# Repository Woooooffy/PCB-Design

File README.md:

# PCB-Design
# Contains my project files
# Hug-sensing IoT plush: a pair of plushies that detects hugs on one end and triggers response in the other. Inspired by Becky and Xyla's project https://beckystern.com/2023/11/27/hug-sensing-iot-parihug-toy-w-xyla-foxlin/ and part of the MIT 2024 PCB design class

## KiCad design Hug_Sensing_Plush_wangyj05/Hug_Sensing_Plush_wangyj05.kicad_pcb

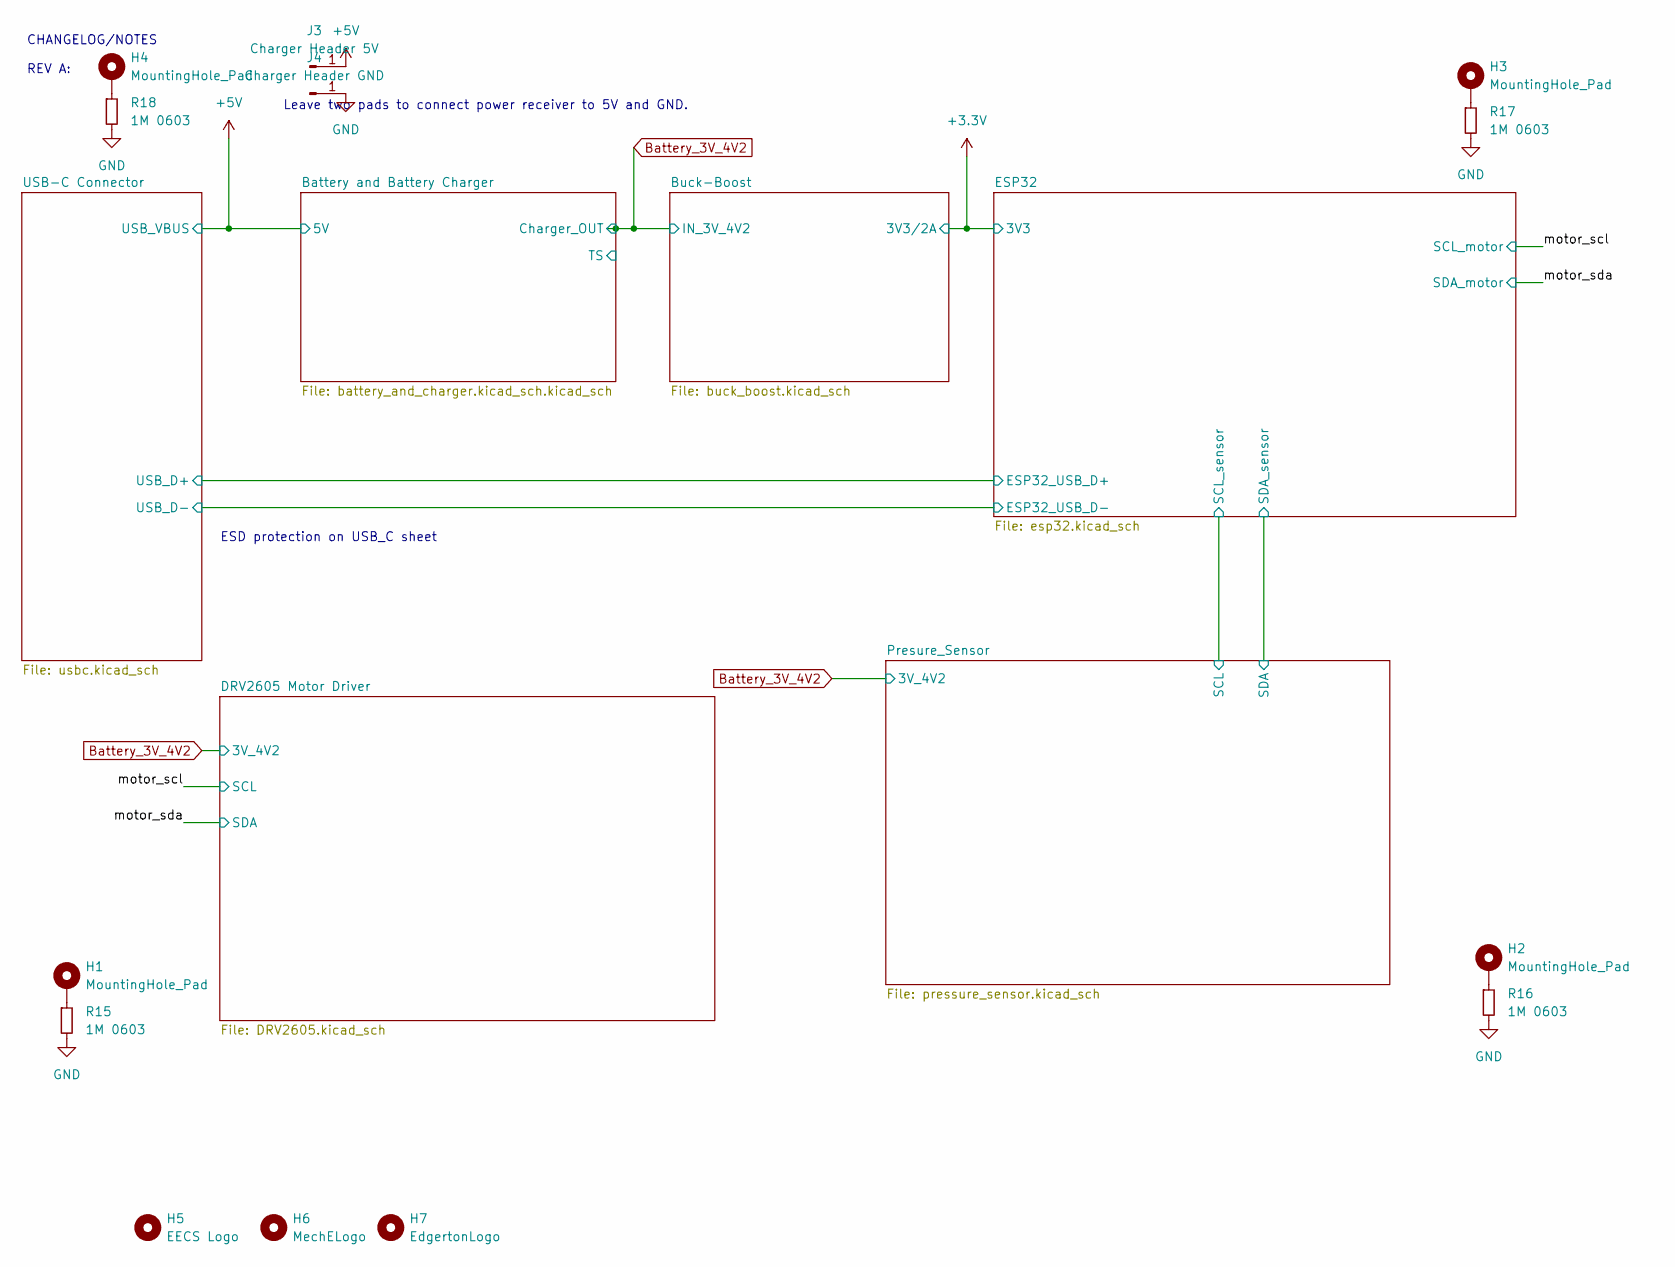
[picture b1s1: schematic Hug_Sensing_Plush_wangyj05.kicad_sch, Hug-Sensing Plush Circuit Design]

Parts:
H1, H2, H3, H4: MountingHole_Pad; MountingHole_2.2mm_M2_DIN965_Pad
H5: EECS Logo; EECSLogo
H6: MechELogo
H7: EdgertonLogo
J3: Charger Header 5V; SolderWirePad_1x01_SMD_1x2mm
J4: Charger Header GND; SolderWirePad_1x01_SMD_1x2mm
R15, R16, R17, R18: 1M 0603; R_0603_1608Metric_Pad0.98x0.95mm_HandSolder; MPN CRCW06031M00JNEAC; Digikey PN 541-CRCW06031M00JNEACCT-ND

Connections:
+5V: J3.1; also elsewhere on the board
GND: J4.1, R15.2, R16.2, R17.2, R18.2; also elsewhere on the board
unnamed: H1.1, R15.1
unnamed: H2.1, R16.1
unnamed: H3.1, R17.1
unnamed: H4.1, R18.1

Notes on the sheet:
ESD protection on USB_C sheet
Leave two pads to connect power receiver to 5V and GND.
CHANGELOG/NOTES REV A:

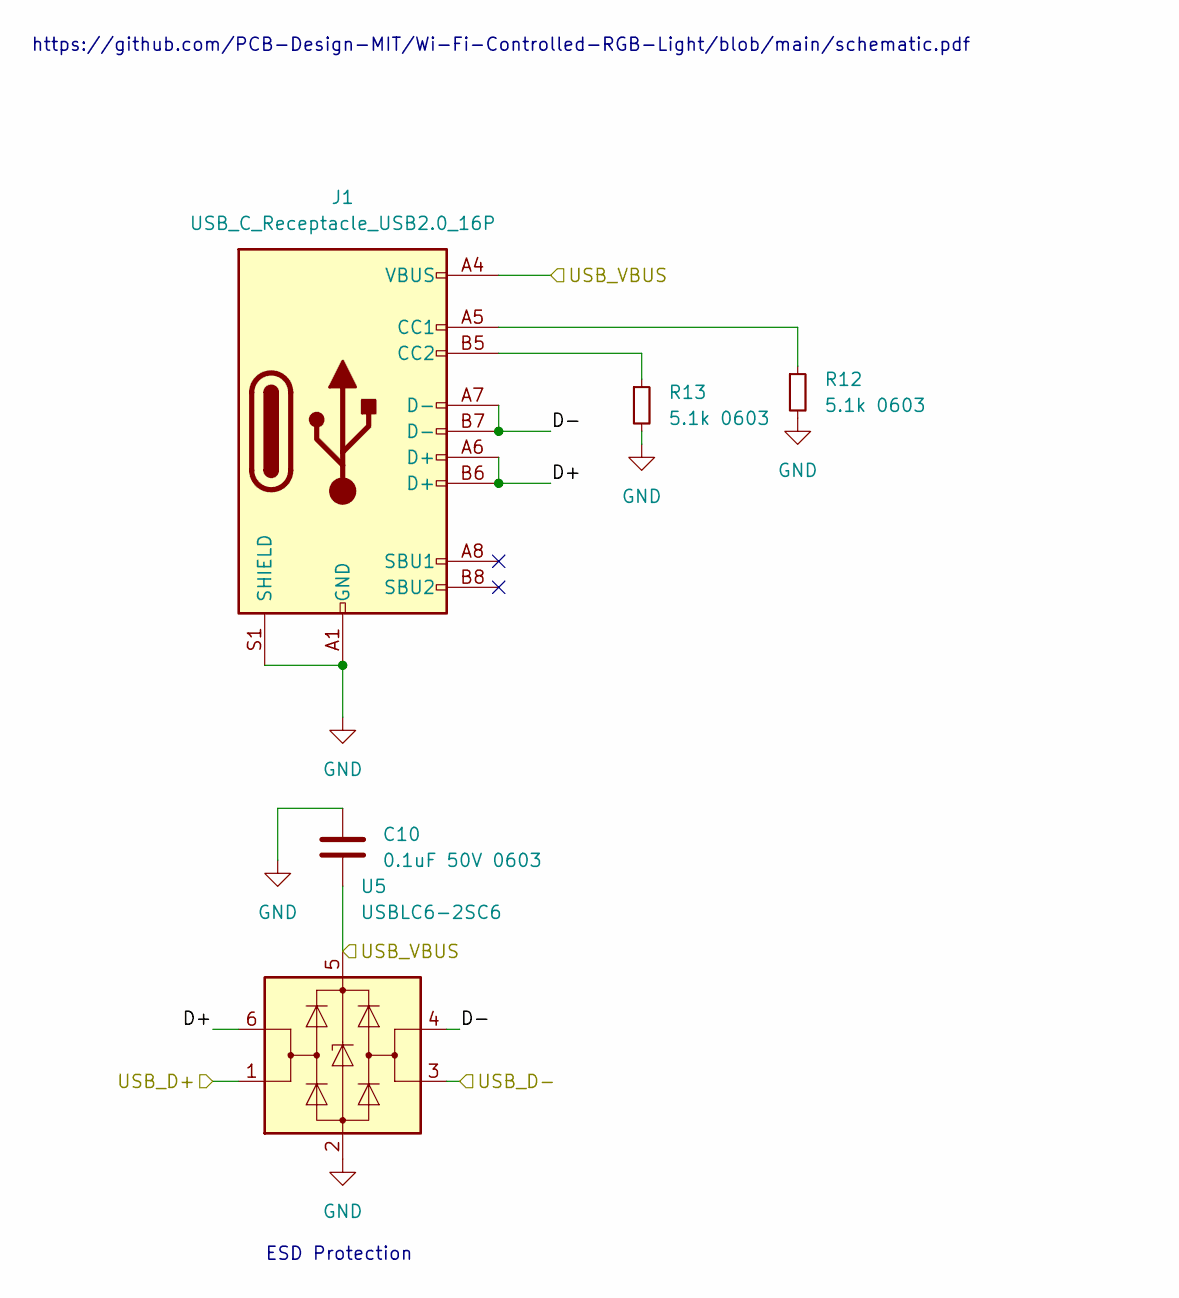
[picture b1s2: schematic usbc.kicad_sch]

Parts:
C10: 0.1uF 50V 0603; C_0603_1608Metric_Pad1.08x0.95mm_HandSolder; MPN CL10B104KB8NNNL; Digikey PN 1276-CL10B104KB8NNNLCT-ND
J1: USB_C_Receptacle_USB2.0_16P; USB_C_Receptacle_GCT_USB4085; MPN USB4085-GF-A; Digikey PN 2073-USB4085-GF-ACT-ND
R12, R13: 5.1k 0603; R_0603_1608Metric_Pad0.98x0.95mm_HandSolder; MPN CRCW06035K10FKEBC; Digikey PN 541-CRCW06035K10FKEBCDKR-ND
U5: USBLC6-2SC6; SOT-23-6; MPN USBLC6-2SC6; Digikey PN 497-5235-1-ND

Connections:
+5V: C10.2, J1.A4 (VBUS), J1.A9 (VBUS), J1.B4 (VBUS), J1.B9 (VBUS), U5.5 (VBUS); also elsewhere on the board
/ESP32/ESP32_USB_D+: U5.1 (I/O1); also elsewhere on the board
/ESP32/ESP32_USB_D-: U5.3 (I/O2); also elsewhere on the board
/USB-C Connector/D+: J1.A6 (D+), J1.B6 (D+), U5.6 (I/O1)
/USB-C Connector/D-: J1.A7 (D-), J1.B7 (D-), U5.4 (I/O2)
GND: C10.1, J1.A1 (GND), J1.A12 (GND), J1.B1 (GND), J1.B12 (GND), J1.S1 (SHIELD), R12.2, R13.2, U5.2 (GND); also elsewhere on the board
unnamed: J1.A5 (CC1), R12.1
unnamed: J1.B5 (CC2), R13.1

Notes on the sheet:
https://github.com/PCB-Design-MIT/Wi-Fi-Controlled-RGB-Light/blob/main/schematic.pdf
ESD Protection

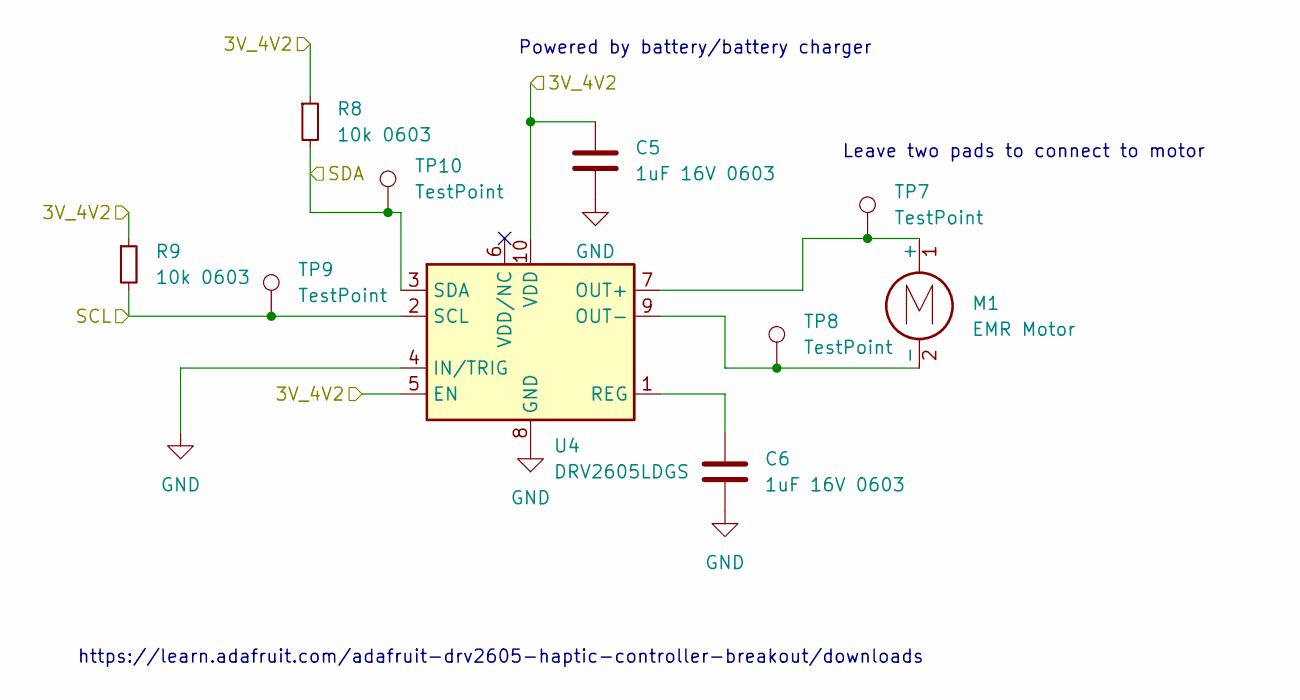
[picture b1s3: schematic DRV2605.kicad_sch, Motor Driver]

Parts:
C5, C6: 1uF 16V 0603; C_0603_1608Metric_Pad1.08x0.95mm_HandSolder; MPN CL10A105KO8NNNC; Digikey PN 1276-1034-1-ND
M1: EMR Motor; MPN 1201; Digikey PN 1528-1177-ND
R8, R9: 10k 0603; R_0603_1608Metric_Pad0.98x0.95mm_HandSolder; MPN CRCW060310K0FKEA; Digikey PN 541-10.0KHCT-ND
TP7, TP8, TP9, TP10: TestPoint; TestPoint_Keystone_5015_Micro-Minature; MPN RCWCTE; Digikey PN 2019-RCWCTECT-ND
U4: DRV2605LDGS; VSSOP-10_3x3mm_P0.5mm; MPN DRV2605LDGSR; Digikey PN 296-40032-1-ND

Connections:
/motor_scl: R9.2, TP9.1, U4.2 (SCL); also elsewhere on the board
/motor_sda: R8.2, TP10.1, U4.3 (SDA); also elsewhere on the board
Battery_3V_4V2: C5.1, R8.1, R9.1, U4.5 (EN), U4.10 (VDD); also elsewhere on the board
GND: C5.2, C6.2, U4.4 (IN/TRIG), U4.8 (GND); also elsewhere on the board
unnamed: M1.1 (+), TP7.1, U4.7 (OUT+)
unnamed: M1.2 (-), TP8.1, U4.9 (OUT-)
unnamed: C6.1, U4.1 (REG)

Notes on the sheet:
https://learn.adafruit.com/adafruit-drv2605-haptic-controller-breakout/downloads
Leave two pads to connect to motor
Powered by battery/battery charger

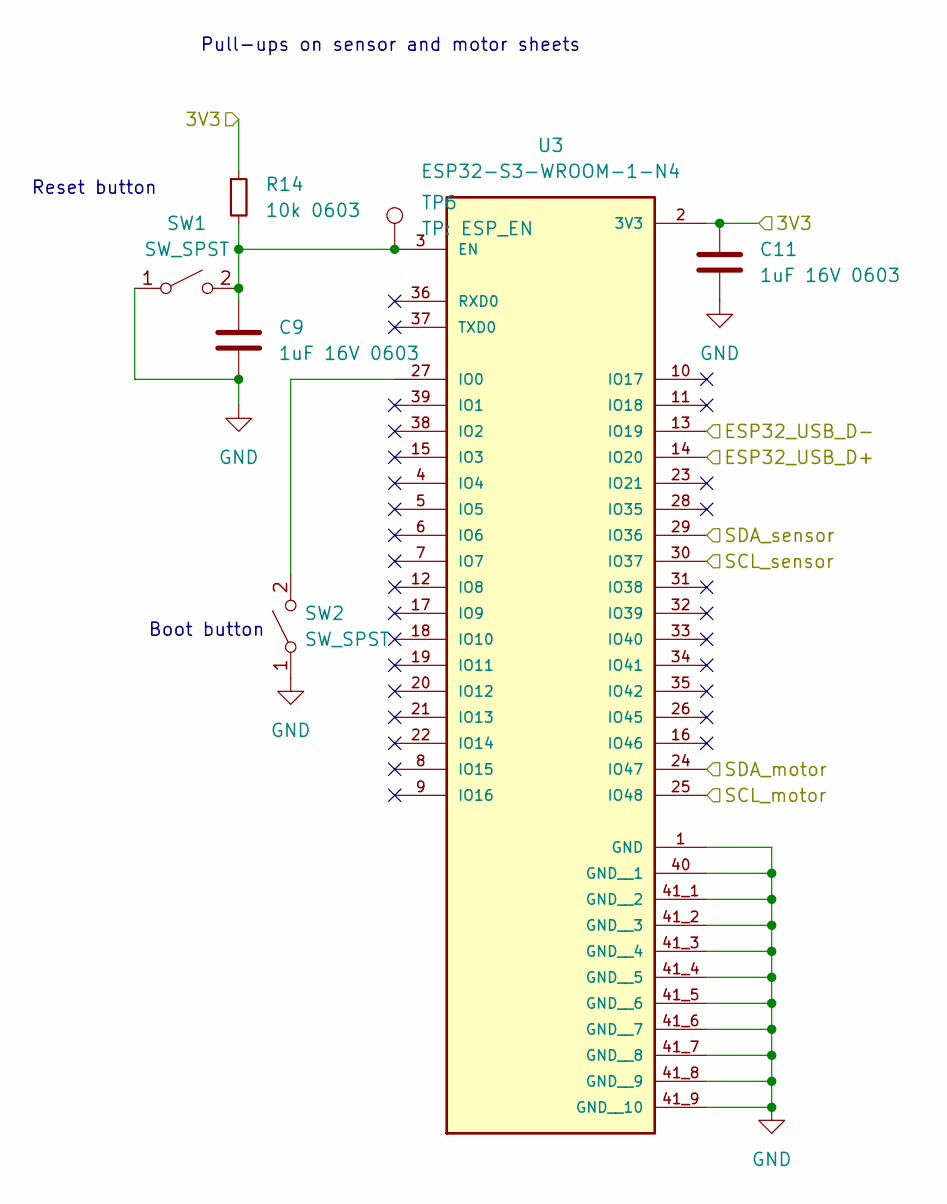
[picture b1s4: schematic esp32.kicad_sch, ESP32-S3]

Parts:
C9, C11: 1uF 16V 0603; C_0603_1608Metric_Pad1.08x0.95mm_HandSolder; MPN CL10A105KO8NNNC; Digikey PN 1276-1034-1-ND
R14: 10k 0603; R_0603_1608Metric_Pad0.98x0.95mm_HandSolder; MPN CRCW060310K0FKEA; Digikey PN 541-10.0KHCT-ND
SW1, SW2: SW_SPST; SW_SPST_FSMSM
TP6: TP: ESP_EN; TestPoint_Keystone_5015_Micro-Minature; MPN RCWCTE; Digikey PN 2019-RCWCTECT-ND
U3: ESP32-S3-WROOM-1-N4; ESP32-S3; PARTREV v1.0; Digikey PN 1965-ESP32-S3-WROOM-1-N4CT-ND

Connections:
+3.3V: C11.1, R14.1, U3.2 (3V3); also elsewhere on the board
/ESP32/ESP32_USB_D+: U3.14 (IO20); also elsewhere on the board
/ESP32/ESP32_USB_D-: U3.13 (IO19); also elsewhere on the board
/ESP32/SCL_sensor: U3.30 (IO37); also elsewhere on the board
/ESP32/SDA_sensor: U3.29 (IO36); also elsewhere on the board
/motor_scl: U3.25 (IO48); also elsewhere on the board
/motor_sda: U3.24 (IO47); also elsewhere on the board
GND: C9.2, C11.2, SW1.1 (A), SW2.1 (A), U3.1 (GND), U3.40 (GND__1), U3.41_1 (GND__2), U3.41_2 (GND__3), U3.41_3 (GND__4), U3.41_4 (GND__5), U3.41_5 (GND__6), U3.41_6 (GND__7), U3.41_7 (GND__8), U3.41_8 (GND__9), U3.41_9 (GND__10), U3.41_10, U3.41_11, U3.41_12, U3.41_13, U3.41_14, U3.41_15, U3.41_16, U3.41_17, U3.41_18, U3.41_19, U3.41_20, U3.41_21; also elsewhere on the board
unnamed: C9.1, R14.2, SW1.2 (B), TP6.1, U3.3 (EN)
unnamed: SW2.2 (B), U3.27 (IO0)

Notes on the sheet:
Pull-ups on sensor and motor sheets
Boot button
Reset button

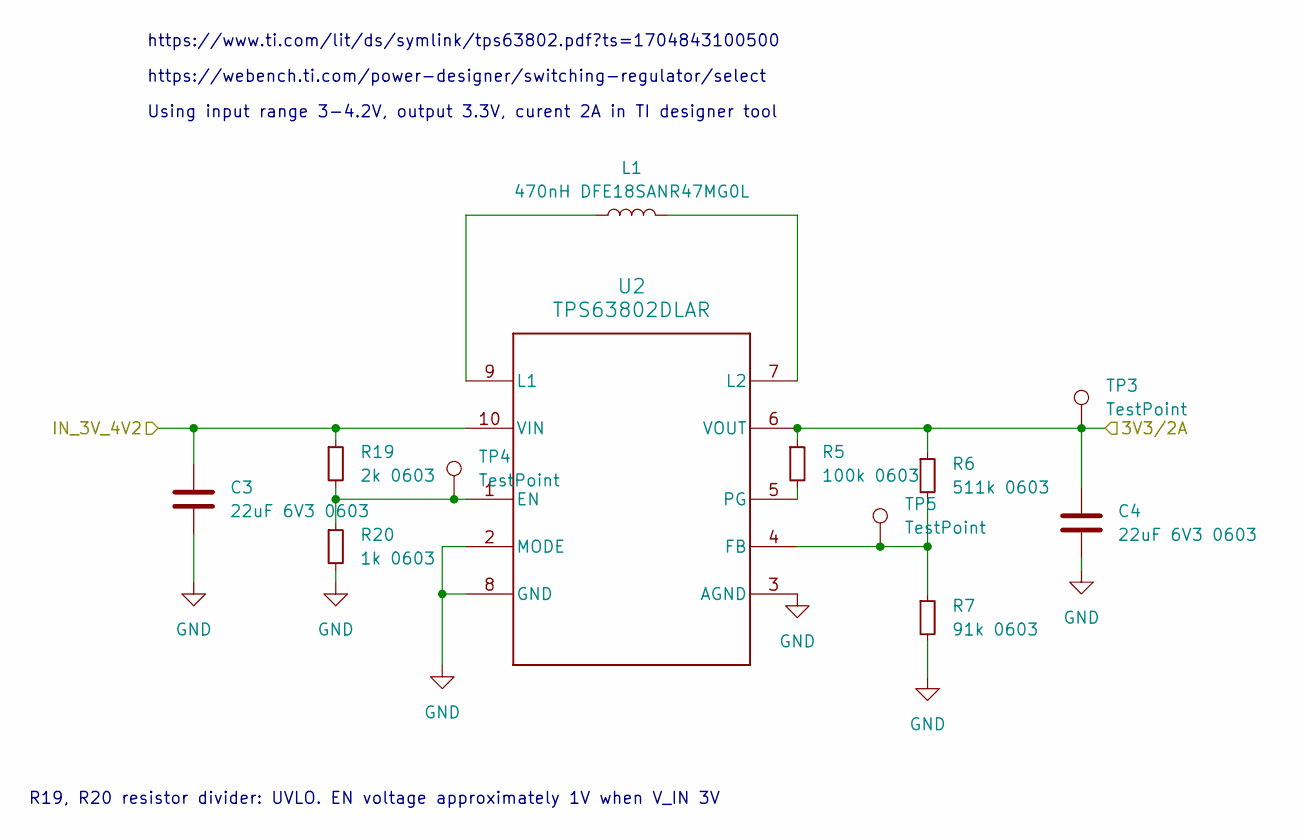
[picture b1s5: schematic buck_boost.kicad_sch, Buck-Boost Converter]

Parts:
C3, C4: 22uF 6V3 0603; C_0603_1608Metric_Pad1.08x0.95mm_HandSolder; MPN GRM188R60J226MEA0; Digikey PN 490-7612-2-ND
L1: 470nH DFE18SANR47MG0L; L_0603_1608Metric_Pad1.05x0.95mm_HandSolder; MPN DFE18SANR47MG0L; Digikey PN 490-16581-1-ND
R5: 100k 0603; R_0603_1608Metric_Pad0.98x0.95mm_HandSolder; MPN CRCW0603100KFKEA; Digikey PN 541-100KHCT-ND
R6: 511k 0603; R_0603_1608Metric_Pad0.98x0.95mm_HandSolder; MPN CRCW0603511KFKEA; Digikey PN 541-511KHCT-ND
R7: 91k 0603; R_0603_1608Metric_Pad0.98x0.95mm_HandSolder; MPN CRCW060391K0FKEAC; Digikey PN 541-5595-1-ND
R19: 2k 0603; R_0603_1608Metric_Pad0.98x0.95mm_HandSolder; MPN CRCW06032K00FKEB; Digikey PN 541-CRCW06032K00FKEBCT-ND
R20: 1k 0603; R_0603_1608Metric_Pad0.98x0.95mm_HandSolder; MPN CRCW06031K00FKEA; Digikey PN 541-1.00KHCT-ND
TP3, TP4, TP5: TestPoint; TestPoint_Keystone_5015_Micro-Minature; MPN RCWCTE; Digikey PN 2019-RCWCTECT-ND
U2: TPS63802DLAR; TPS63802; MPN TPS63802DLAR; Digikey PN 296-TPS63802DLARCT-ND

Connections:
+3.3V: C4.1, R5.1, R6.1, TP3.1, U2.6 (VOUT); also elsewhere on the board
Battery_3V_4V2: C3.1, R19.1, U2.10 (VIN); also elsewhere on the board
GND: C3.2, C4.2, R7.2, R20.2, U2.2 (MODE), U2.3 (AGND), U2.8 (GND); also elsewhere on the board
unnamed: R19.2, R20.1, TP4.1, U2.1 (EN)
unnamed: R6.2, R7.1, TP5.1, U2.4 (FB)
unnamed: L1.1, U2.9 (L1)
unnamed: L1.2, U2.7 (L2)
unnamed: R5.2, U2.5 (PG)

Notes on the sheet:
https://webench.ti.com/power-designer/switching-regulator/select
https://www.ti.com/lit/ds/symlink/tps63802.pdf?ts=1704843100500
R19, R20 resistor divider: UVLO. EN voltage approximately 1V when V_IN 3V
Using input range 3-4.2V, output 3.3V, curent 2A in TI designer tool

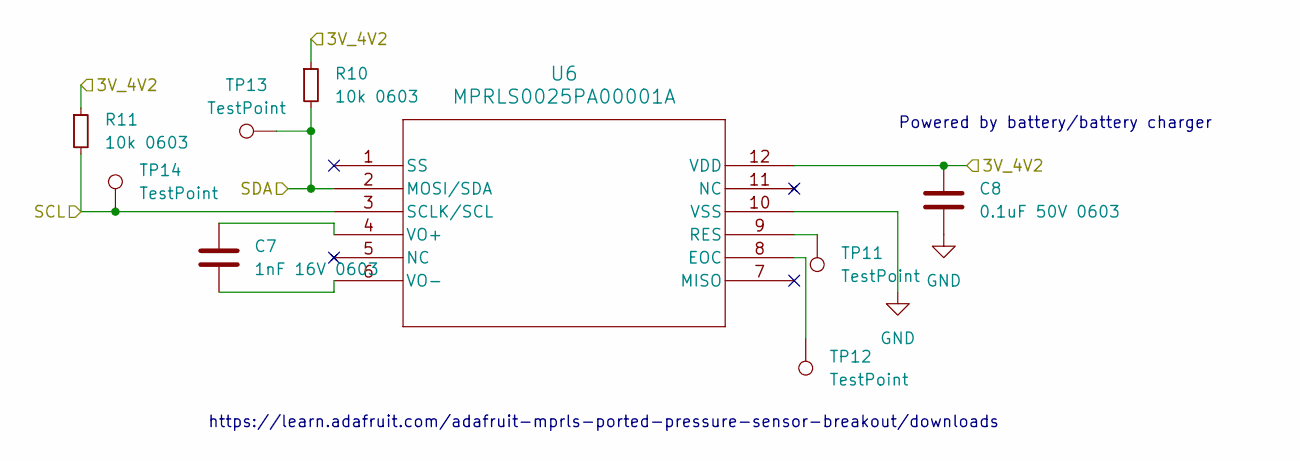
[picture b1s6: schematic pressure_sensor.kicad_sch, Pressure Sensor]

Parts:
C7: 1nF 16V 0603; C_0603_1608Metric_Pad1.08x0.95mm_HandSolder; MPN C0603C102K4RECAUTO; Digikey PN 399-17878-1-ND
C8: 0.1uF 50V 0603; C_0603_1608Metric_Pad1.08x0.95mm_HandSolder; MPN CL10B104KB8NNNL; Digikey PN 1276-CL10B104KB8NNNLCT-ND
R10, R11: 10k 0603; R_0603_1608Metric_Pad0.98x0.95mm_HandSolder; MPN CRCW060310K0FKEA; Digikey PN 541-10.0KHCT-ND
TP11, TP12, TP13, TP14: TestPoint; TestPoint_Keystone_5015_Micro-Minature; MPN RCWCTE; Digikey PN 2019-RCWCTECT-ND
U6: MPRLS0025PA00001A; MPRLS; MPN MPRLS0025PA00001A; Digikey PN 480-7098-1-ND

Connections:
/ESP32/SCL_sensor: R11.2, TP14.1, U6.3 (SCLK/SCL); also elsewhere on the board
/ESP32/SDA_sensor: R10.2, TP13.1, U6.2 (MOSI/SDA); also elsewhere on the board
Battery_3V_4V2: C8.1, R10.1, R11.1, U6.12 (VDD); also elsewhere on the board
GND: C8.2, U6.10 (VSS); also elsewhere on the board
unnamed: TP12.1, U6.8 (EOC)
unnamed: TP11.1, U6.9 (RES)
unnamed: C7.1, U6.4 (VO+)
unnamed: C7.2, U6.6 (VO-)

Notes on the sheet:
https://learn.adafruit.com/adafruit-mprls-ported-pressure-sensor-breakout/downloads
Powered by battery/battery charger

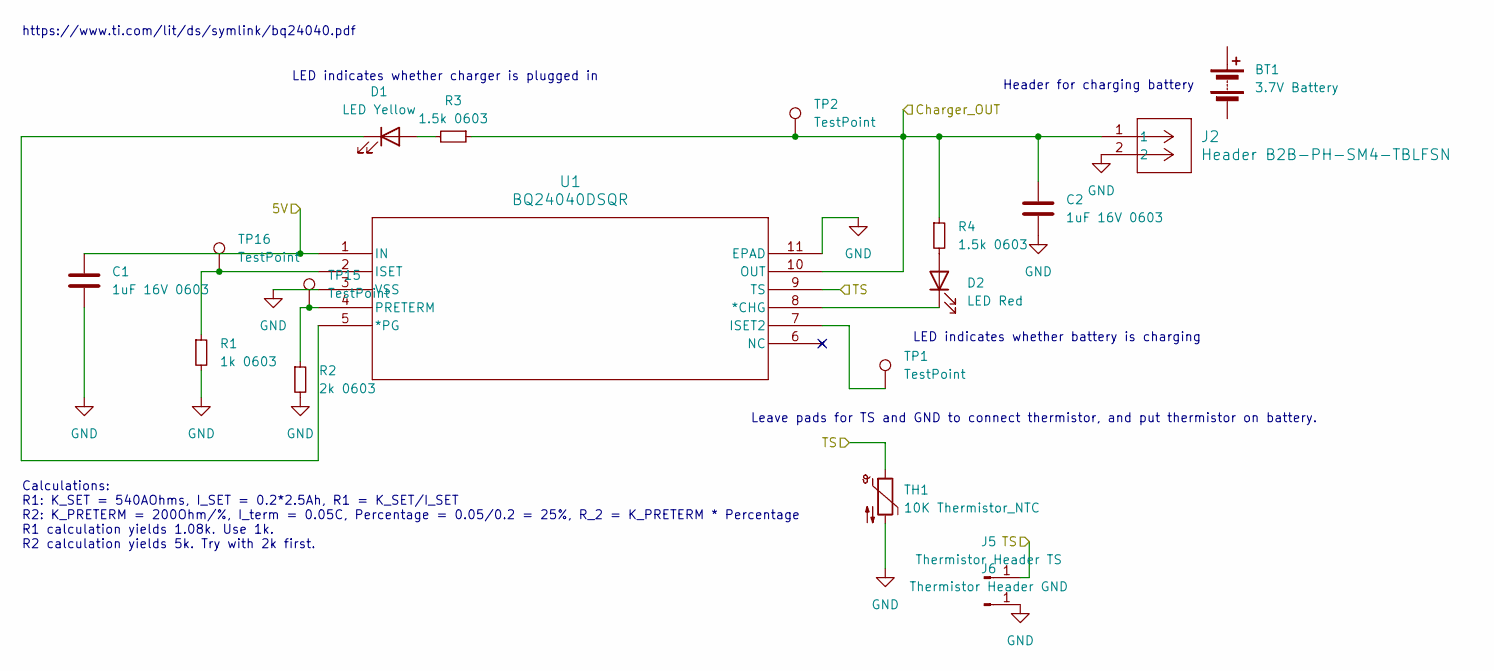
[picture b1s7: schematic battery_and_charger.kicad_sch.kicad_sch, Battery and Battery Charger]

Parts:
BT1: 3.7V Battery; MPN 328; Digikey PN 1528-1840-ND
C1, C2: 1uF 16V 0603; C_0603_1608Metric_Pad1.08x0.95mm_HandSolder; MPN CL10A105KO8NNNC; Digikey PN 1276-1034-1-ND
D1: LED Yellow; LED_0603_1608Metric_Pad1.05x0.95mm_HandSolder; MPN LTST-C190KSKT; Digikey PN 160-1437-1-ND
D2: LED Red; LED_0603_1608Metric_Pad1.05x0.95mm_HandSolder; MPN LTST-C190EKT; Digikey PN 160-1182-1-ND
J2: Header B2B-PH-SM4-TBLFSN; CONN_B2B-PH-SM4-TBLFSN_JST(Header); MPN B2B-PH-SM4-TB; Digikey PN 455-B2B-PH-SM4-TBCT-ND
J5: Thermistor Header TS; SolderWirePad_1x01_SMD_1x2mm
J6: Thermistor Header GND; SolderWirePad_1x01_SMD_1x2mm
R1: 1k 0603; R_0603_1608Metric_Pad0.98x0.95mm_HandSolder; MPN CRCW06031K00FKEA; Digikey PN 541-1.00KHCT-ND
R2: 2k 0603; R_0603_1608Metric_Pad0.98x0.95mm_HandSolder; MPN CRCW06032K00FKEB; Digikey PN 541-CRCW06032K00FKEBCT-ND
R3, R4: 1.5k 0603; R_0603_1608Metric_Pad0.98x0.95mm_HandSolder; MPN CRCW06031K50FKEB; Digikey PN 541-CRCW06031K50FKEBCT-ND
TH1: 10K Thermistor_NTC; MPN 4890; Digikey PN 1528-4890-ND
TP1, TP2, TP15, TP16: TestPoint; TestPoint_Keystone_5015_Micro-Minature; MPN RCWCTE; Digikey PN 2019-RCWCTECT-ND
U1: BQ24040DSQR; BQ24040; MPN BQ24040DSQR; Digikey PN 296-37142-1-ND

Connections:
+5V: C1.1, U1.1 (IN); also elsewhere on the board
/Battery and Battery Charger/TS: J5.1, TH1.1, U1.9 (TS)
Battery_3V_4V2: C2.1, J2.1, R3.1, R4.1, TP2.1, U1.10 (OUT); also elsewhere on the board
GND: C1.2, C2.2, J2.2, J2.3, J2.4, J6.1, R1.2, R2.2, TH1.2, U1.3 (VSS), U1.11 (EPAD), U1.V; also elsewhere on the board
unnamed: D1.2 (A), R3.2
unnamed: D1.1 (K), U1.5 (*PG)
unnamed: D2.2 (A), R4.2
unnamed: D2.1 (K), U1.8 (*CHG)
unnamed: TP1.1, U1.7 (ISET2)
unnamed: R1.1, TP16.1, U1.2 (ISET)
unnamed: R2.1, TP15.1, U1.4 (PRETERM)

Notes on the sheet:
Header for charging battery
LED indicates whether battery is charging
Leave pads for TS and GND to connect thermistor, and put thermistor on battery.
Calculations: R1: K_SET = 540AOhms, I_SET = 0.2*2.5Ah, R1 = K_SET/I_SET R2: K_PRETERM = 200Ohm/%, I_term = 0.05C, Percentage = 0.05/0.2 = 25%, R_2 = K_PRETERM * Percentage R1 calculation yields 1.08k. Use 1k. R2 calculation yields 5k. Try with 2k first.
https://www.ti.com/lit/ds/symlink/bq24040.pdf
LED indicates whether charger is plugged in

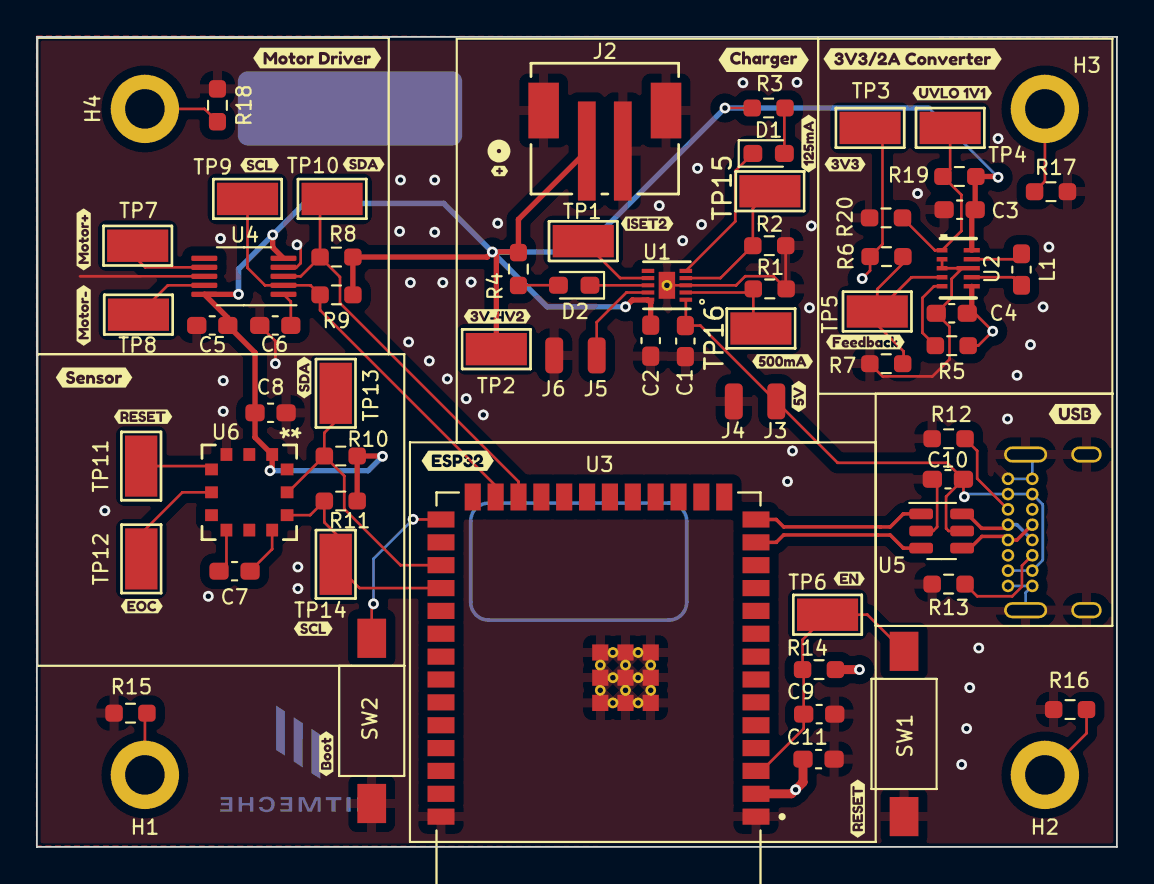
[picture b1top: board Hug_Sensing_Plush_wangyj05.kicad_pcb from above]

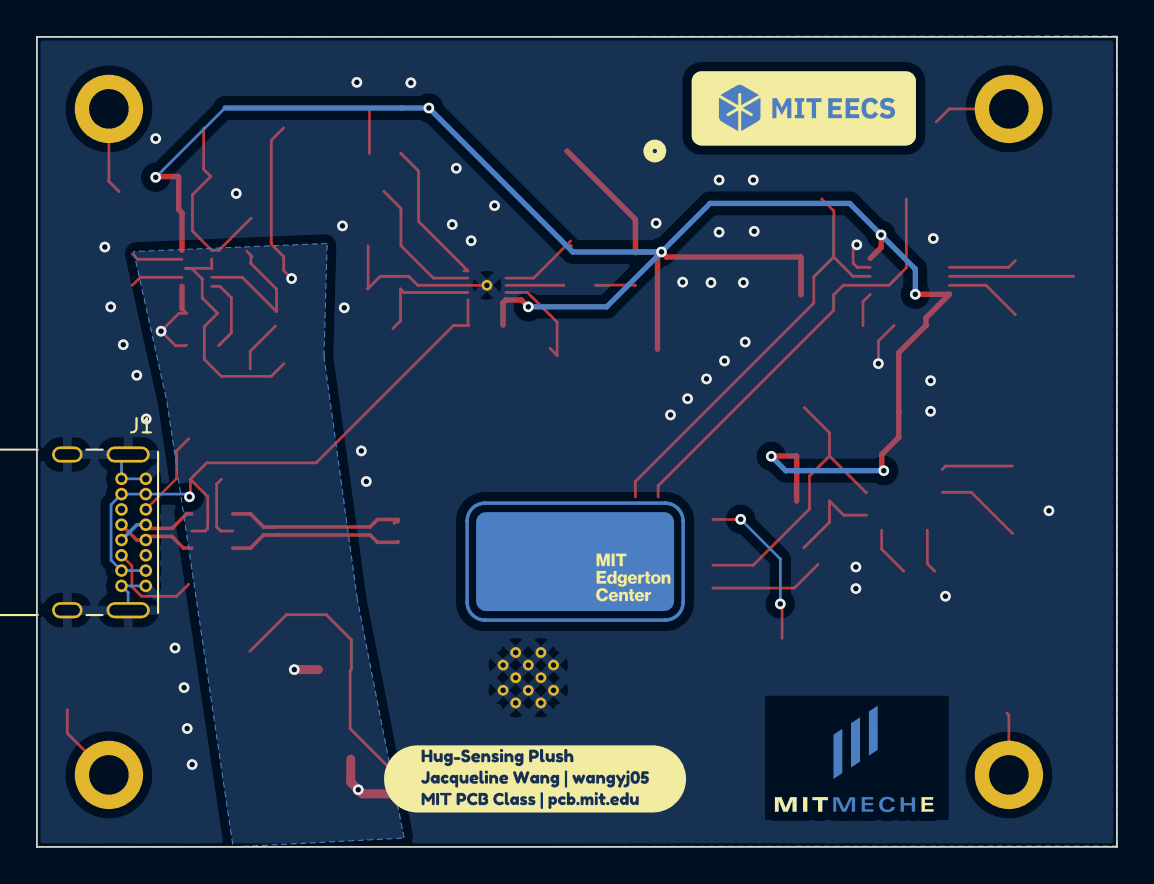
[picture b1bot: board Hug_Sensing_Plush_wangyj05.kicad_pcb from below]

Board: 2 copper layers, 60.0 x 45.0 mm, 98 parts (5 on the bottom side), 40 nets.

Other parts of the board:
kibuzzard-65AAE9C3: G***; kibuzzard-65AAE9C3
kibuzzard-65AAE9E5: G***; kibuzzard-65AAE9E5
kibuzzard-65AAEA4C: G***; kibuzzard-65AAEA4C
kibuzzard-65AAEA37: G***; kibuzzard-65AAEA37
kibuzzard-65AAEA43: G***; kibuzzard-65AAEA43
kibuzzard-65AAEA55: G***; kibuzzard-65AAEA55
kibuzzard-65AAEA96: G***; kibuzzard-65AAEA96
kibuzzard-65AAEAAB: G***; kibuzzard-65AAEAAB
kibuzzard-65AAEAD5: G***; kibuzzard-65AAEAD5
kibuzzard-65AAEADF: G***; kibuzzard-65AAEADF
kibuzzard-65AAEB64: G***; kibuzzard-65AAEB64
kibuzzard-65AAEBD9: G***; kibuzzard-65AAEBD9
kibuzzard-65AAEBEE: G***; kibuzzard-65AAEBEE
kibuzzard-65AAECF1: G***; kibuzzard-65AAECF1
kibuzzard-65AAF1CD: G***; kibuzzard-65AAF1CD
kibuzzard-65AAF1FE: G***; kibuzzard-65AAF1FE
kibuzzard-65AAF2C1: G***; kibuzzard-65AAF2C1
kibuzzard-65AAF2E5: G***; kibuzzard-65AAF2E5
kibuzzard-65AAF3AD: G***; kibuzzard-65AAF3AD
kibuzzard-65AAF7C7: G***; kibuzzard-65AAF7C7
kibuzzard-65AAF38A: G***; kibuzzard-65AAF38A
kibuzzard-65AAF39C: G***; kibuzzard-65AAF39C
kibuzzard-65AAF250: G***; kibuzzard-65AAF250
kibuzzard-65AAF270: G***; kibuzzard-65AAF270
kibuzzard-65AAF304: G***; kibuzzard-65AAF304
kibuzzard-65AAF374: G***; kibuzzard-65AAF374
kibuzzard-65AAF394: G***; kibuzzard-65AAF394

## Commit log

2024-01-15 Hug sensing plush design with KiCAD
2024-01-16 Hug-Sensing IoT Plush
2024-01-16 Removed some files
2024-01-16 DS_Store
2024-01-16 Lab01 Files
2024-01-17 Edited board layout
2024-01-18 Updated layout
2024-01-19 Edited PCB layout
2024-01-19 Updated board layout
2024-01-20 Edited file names
2024-01-27 Added more references
2024-01-27 Added bring-up plan
